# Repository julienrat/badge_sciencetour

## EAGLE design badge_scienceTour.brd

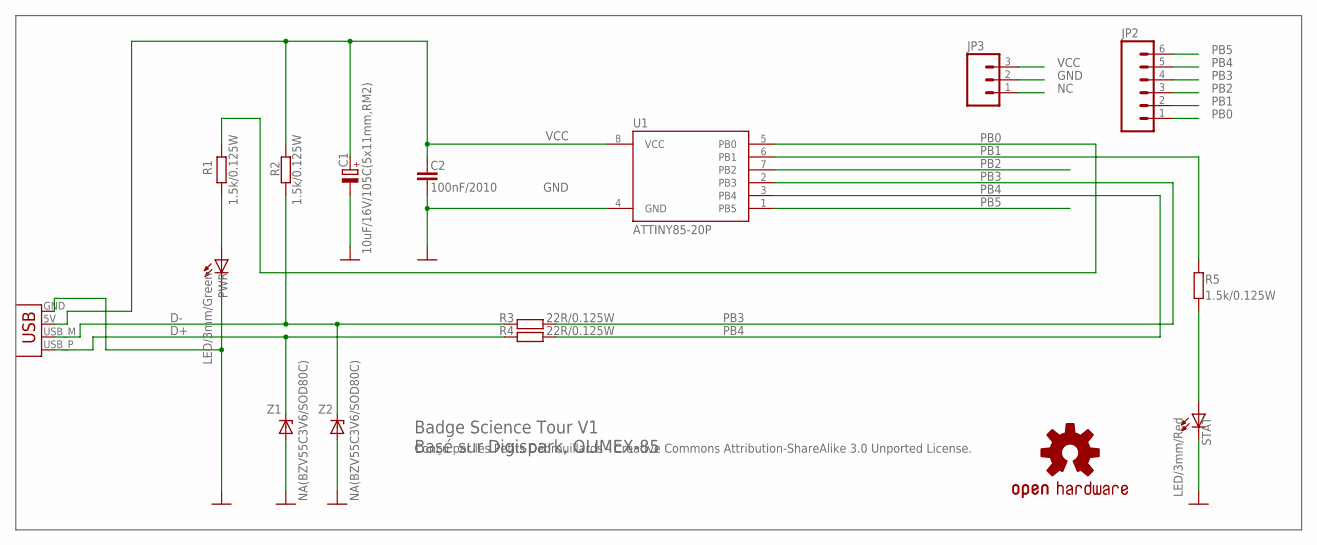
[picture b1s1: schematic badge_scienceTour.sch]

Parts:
C1: 10uF/16V/105C(5x11mm,RM2); E2-5
C2: 100nF/2010; C025-025X050
JP1: USBPCB; USB-A-PCB
JP2: M06NO_SILK; 1X06_NO_SILK
JP3: M031X03_NO_SILK; 1X03_NO_SILK
LOGO1: OSHW-LOGOS; OSHW-LOGO-S
PWR: LED/3mm/Green; LED3MM
R1, R2, R5: 1.5k/0.125W; 0204/5
R3, R4: 22R/0.125W; 0204/5
STAT: LED/3mm/Red; LED3MM
U1: ATTINY85-20P; PDIP08_300MIL
Z1, Z2: NA(BZV55C3V6/SOD80C); ZDIO-5

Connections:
D+: JP1.USB_P (D+), R4.1, Z1.C
D-: JP1.USB_M (D-), R2.1, R3.1, Z2.C
GND: C1.-, C2.2, JP1.GND, JP3.2, PWR.K (C), STAT.K (C), U1.4 (GND), Z1.A, Z2.A
unnamed: PWR.A, R1.1
unnamed: R5.1, STAT.A
NC: JP3.1
PB0: JP2.1, R1.2, U1.5 (PB0)
PB1: JP2.2, R5.2, U1.6 (PB1)
PB2: JP2.3, U1.7 (PB2)
PB3: JP2.4, R3.2, U1.2 (PB3)
PB4: JP2.5, R4.2, U1.3 (PB4)
PB5: JP2.6, U1.1 (PB5)
VCC: C1.+, C2.1, JP1.5V (VBUS), JP3.3, R2.2, U1.8 (VCC)

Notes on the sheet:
Badge Science Tour V1 Basé sur Digispark, OLIMEX-85
Conçu par les Petits Débrouillards - Creative Commons Attribution-ShareAlike 3.0 Unported License.

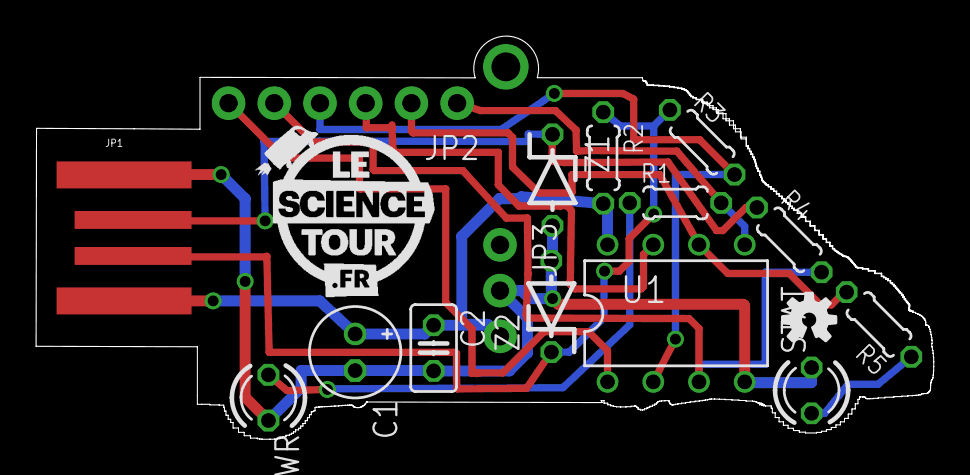
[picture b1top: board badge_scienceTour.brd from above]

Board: 2 copper layers, 49.9 x 22.4 mm, 16 parts (0 on the bottom side), 12 nets.

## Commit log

2014-06-12 + ‘.sparkleshare’ + ‘SparkleShare.txt’
2014-06-12 + ‘LOGO-SCIENCE-TOUR-BUS-e1369822406782.bmp’ + ‘badge_scienceTour.GBP’ + ‘badge_scienceTour.GTP’ + ‘badge_scienceTour.b#1’ + ‘badge_scienceTour.b#2’ + ‘badge_scienceTour.brd’ + ‘badge_scienceTour.dri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
2014-06-30 + ‘librairie fritzing/’ + ‘librairie fritzing/Badge du scienceTour.fzpz’

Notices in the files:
parts and their libraries:
SparkFun-Connectors: Licensing: Creative Commons ShareAlike 4.0 International - https://creativecommons.org/licenses/by-sa/4.0
